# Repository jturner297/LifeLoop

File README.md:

# LifeLoop iOS App Documentation

## Overview
LifeLoop is an iOS application built with SwiftUI, integrating Bluetooth Low Energy (BLE) hardware telemetry monitoring, location services via CoreLocation, AWS Amplify with Cognito User Pools and AppSync GraphQL services for family health monitoring, hardware check-in pinging, real-time alert subscriptions, and emergency dispatching.

---

## Architecture & Core Components

### 1. Application Lifecycle & Configuration
* **App Initialization (`LifeLoopApp`):** Configures AWS Amplify (Auth and API plugins) and requests user notification authorizations (`.alert`, `.sound`, `.badge`) on app launch.
* **Bundle Identifier:** Configured dynamically via Xcode build target settings.

### 2. UI & User Flows

#### Root Navigation & Onboarding (`AppRootView`, `AccountSetupView`, `WelcomeView`)
* **Initial Setup Flow:**
  * If account setup is incomplete, the app presents `AccountSetupView` for AWS Cognito authentication (sign in, sign up, email verification code, password reset, challenge/MFA, or option to skip/continue without an account).
  * If account setup is complete but onboarding has not finished, `WelcomeView` prompts the user for their name, optional phone number, email address, and contact sharing consent.
  * Once onboarded, the app displays the main tab interface (`ContentView`).

#### Main Application Navigation (`ContentView`)
* **Tab Navigation:** Houses a 4-tab bottom navigation interface:
  1. **Home:** Main dashboard featuring user greeting, member/device search bar, view filters (Home, Family, Map), local device quick cards, manual "Call Help" emergency button, persistent emergency cancellation failure cards, and group member lists.
  2. **Devices:** Lists all saved LifeLoop BLE hardware peripherals, connection statuses, battery levels, and controls for connecting new peripherals.
  3. **Groups:** Displays family groups, invitation codes, member management, call contacts, and shared device configurations.
  4. **Profile:** Displays user profile details, privacy settings, notification configurations, and account management options.

#### Home Tab (`ContentView`)
* **Manual Emergency Call:** Provides a prominent "Call Help" button to initiate the emergency countdown (`EMSTimerManager`) and issue an `SOS` command to connected BLE devices.
* **Cloud Cancellation Warning Card:** Displays a prominent yellow warning card directly above the emergency button if a cloud emergency cancellation attempt fails on AWS, allowing the wearer to retry cloud cancellation explicitly without restarting an alert.
* **Search & Filters:** Enables filtering by Home view, Family member cards, or interactive group map view.

#### Devices Tab & Device Profiles (`ContentView`, `DeviceProfileSheet`, `AddDeviceSheet`)
* **BLE Device List:** Displays saved hardware peripherals, live heart rate (BPM), connection status (Connected, Connecting, Offline), and low battery warnings (<= 10%).
* **Add Device Sheet (`AddDeviceSheet`):** Scans for nearby LifeLoop BLE peripherals using `BLEMonitor`, listing discovered devices for one-tap pairing.
* **Device Profile Sheet (`DeviceProfileSheet`):** Shows detailed hardware state, battery level, live BPM, coordinates, last update timestamp, location map preview, raw BLE text payload, connection log, option to rename the device, and an explicit removal alert confirmation that disconnects and purges saved peripheral references.

#### Groups & Family Management (`GroupsView`, `GroupDetailView`, `FamilyManagementViews`)
* **Group Management:**
  * **Create & Join:** Users can create new family groups or join existing ones using an alphanumeric invitation code.
  * **Group Details:** Displays invitation code sharing options, local group nickname customization, list of family members, emergency call contacts, and shared device configurations.
* **Members & Roles (`FamilyMembersView`):**
  * Displays group members and assigned roles (`CREATOR`, `ADMIN`, `MEMBER`).
  * Admin and Creator roles can modify member roles, remove members, or block/unblock users.
* **Emergency Call Contacts (`FamilyContactsView` & `ContactEditor`):**
  * Allows managing up to 10 emergency call contacts per family group.
  * Contact addition requires explicitly validating the contact's name, phone number (E.164 format), and user consent confirmation.
* **Shared Devices (`GroupSharingView`):**
  * Controls which local BLE devices are shared with specific family groups.
* **Member Details & Check-In (`MemberInfoView`):**
  * Shows a family member's telemetry, BPM, online status, reverse-geocoded street address, interactive location map (`MemberMap`), and status of active check-in requests.
  * Includes a **"Send 'Check-In' Ping"** action to send a hardware check-in prompt to the target member's device.

#### Profile & Settings (`ProfileView`, `SettingsView`, `NotificationsView`)
* **User Profile (`ProfileView`):** Displays user initials/avatar, joined family count, and navigation to settings sections.
* **Personal & Privacy Settings (`SettingsView`):**
  * Edits display name, optional birthday (automatically updating calculated user age), phone number, email address, and contact sharing consent.
  * **Privacy Toggles:** Global toggles for `Share location` (`com.lifeloop.family.locationSharingEnabled`) and `Share device information` (`profile.shareDeviceInformation`).
* **Notification Settings (`NotificationsView`):**
  * Configures emergency alerts, call-workflow status updates, and sound toggles.
  * Displays system authorization status, provides a direct link to iOS App Settings, and includes a test notification trigger.

#### Emergency Overlay, Cancellation & Dispatch Status (`EMSCountdown`, `SOSAlertStatusView`)
* **Emergency Countdown (`EMSCountdown` / `EmergencyCountdownScreen`):**
  * Full-screen emergency presentation triggered automatically when a fall or cardiac abnormality is detected, or when manual SOS is pressed.
  * Displays a 30-second countdown ring, trigger reason, dynamic font sizing, accessibility reduce-motion awareness, and an explicit **"I’m OK — Cancel alert"** button.
* **Cancellation Feedback & Retry Alert:**
  * If the wearer cancels an alert but the AWS GraphQL cancellation mutation fails, the screen presents a "Cancellation Unconfirmed" alert prompt with options to retry cancellation or dismiss, ensuring the wearer is explicitly informed that emergency contacts may still be notified.
* **Alert Status (`SOSAlertStatusView`):**
  * Full-screen view presented after the countdown expires while the alert is active on AWS AppSync.
  * Informs the user of dispatch progress, grace period status, and option to request cancellation before emergency calls begin.

---

### 3. Design System & Styling (`LoopStyle`, `LifeLoopBrand`)
* **Color Palette:**
  * `LoopStyle.green` (`#38FF14` / RGB 0.22, 1.0, 0.08)
  * `LoopStyle.mint` (Light background accent)
  * `LoopStyle.background` (Off-white page background)
  * `LoopStyle.ink` (Dark text color)
* **Components & Modifiers:**
  * `.loopCard()`: Styled rounded card container for content blocks.
  * `.loopPage()`: Standard background and tint styling for views.
  * `ProfileAvatar`: Circle avatar rendering initials or fallback icon.
  * `MemberMap`: Standard SwiftUI `Map` wrapper showing member coordinates and fallback states.
  * `LandscapeArt`: Vector gradient and mountain landscape illustration.

---

### 4. Bluetooth Low Energy Integration & Hardware Firmware (`BLEMonitor` & `UpdatedNrfCode.ino`)

#### Hardware Firmware & Hardware State Machine (`UpdatedNrfCode.ino`)
* **Hardware Sensors:** Operates on Arduino-compatible nRF hardware with an LSM6DS3 IMU for accelerometer data and a MAX30105 optical pulse sensor for heart rate DSP. Runs an Edge Impulse Machine Learning model for fall classification.
* **Firmware State Machine (`FallDetection` enum):**
  * `Normal (0)`: Standard monitoring state.
  * `Recovering (3)`: Post-impact observation window.
  * `Emergency (4)`: Fall/Emergency state; flashes red LED and activates 3000 Hz buzzer tone.
  * `Ping (5)`: Check-in request state; flashes blue LED and activates 2000 Hz buzzer tone.
* **Hardware BLE Commands (Received via RX Characteristic):**
  * `"CANCEL"`: Resets state to `Normal (0)`, turns off buzzer, and restores default LEDs.
  * `"SOS"`: Transitions state directly to `Emergency (4)`, activates red LED and 3000 Hz buzzer.
  * `"PING"`: Transitions state to `Ping (5)`, activates blue LED and 2000 Hz buzzer. Pressing the physical hardware button (hold >= 500 ms) acknowledges the check-in and resets state to `Normal (0)`.

#### Hardware BLE Characteristics
* **Service UUID:** `6E400001-B5A3-F393-E0A9-E50E24DCCA9E`
* **TX Characteristic (Notify | Read):** `6E400003-B5A3-F393-E0A9-E50E24DCCA9E` (streams payload: `BPM:%.1f|State:%d\n`).
* **RX Characteristic (Write | Write Without Response):** `6E400002-B5A3-F393-E0A9-E50E24DCCA9E`.

#### iOS BLE Central Manager (`BLEMonitor`)
* **Connection Maintenance (`maintainConnections`):** Automatically scans for missing saved devices and retrieves/reconnects known peripherals unless manually disconnected. State restoration is supported via `LifeLoopCentralManager` restore key.
* **Telemetry Parsing:** Parses standard `BPM:%.1f|State:%d` payloads or JSON structures. Extracts heart rate (`bpm`, `heartrate`, `hr`), state, battery level, and optional location coordinates.
* **Emergency Detection:** Automatically triggers the local countdown timer (`EMSTimerManager.shared.startCountdown`) upon detecting cardiac abnormalities (BPM between 1 and 40) or severe fall state (`State 4`).
* **Device Fall Cancellation:** Detects when the wearer manually cancels an emergency on the physical hardware button (transition from State 3/4 to State 0 without an app cancel pending) and posts a `DeviceCancellationRequest`.
* **Ping Acknowledgment:** Detects when a device in `Ping` state (State 5) transitions to `Normal` (State 0), clears active ping flags, updates sequence counters, and posts a `.lifeLoopPingAcknowledged` notification.
* **BLE Command Methods:**
  * `sendSOSCommand()`: Writes `"SOS"` to the RX characteristic of connected peripherals.
  * `sendCancelCommand()`: Writes `"CANCEL"` to connected peripherals.
  * `sendPingCommand(deviceID:)`: Queues and writes `"PING"` to target or all known peripherals.

---

### 5. Emergency Management (`EMSTimerManager`, `EmergencyAlarmManager`)
* **Countdown Manager (`EMSTimerManager`):**
  * Controls the 30-second emergency countdown timer when cardiac, fall, or manual SOS events occur.
  * Holds reference to `triggerDeviceID`, `triggerReason`, and `callDeadline`.
  * `synchronizeCallDeadline(_ date: Date)`: Synchronizes the local timer deadline with the earliest call time returned by AWS backend alerts.
* **Audio & Haptic Alarm (`EmergencyAlarmManager`):**
  * Pre-loads the emergency alarm audio track into memory at app boot without activating the system audio session.
  * **Lazy Audio Activation & Prioritization:** Dynamically activates `AVAudioSession` with `.playback` category and `.duckOthers` option only when `startAlarm()` is executed during an active emergency, ducking external audio (e.g. Spotify/Apple Music).
  * **Haptic Vibration Loop:** Uses a dedicated `UIImpactFeedbackGenerator` with `.heavy` style triggered on a 0.6-second repeating timer alongside system vibrations.
  * **Audio Session Cleanup:** Calling `stopAlarm()` halts playback, invalidates the haptic timer, resets track timing, and explicitly deactivates the audio session with `.notifyOthersOnDeactivation` to immediately restore background audio volume.

---

### 6. Family Telemetry, Check-Ins & Synchronization (`FamilyDeviceManager`, `LoopNotifications`)
* **Telemetry Upload & Link Optimization:**
  * Periodically syncs connected device telemetry (BPM, state, GPS coordinates, location sharing preferences, online status) with AWS AppSync for linked family devices.
  * Maintains an in-memory `linkedDeviceKeys` set cache (`\(code):\(deviceID):\(displayName)`) to execute `linkDevice` GraphQL mutations only once per device connection, eliminating redundant AWS write operations during continuous telemetry streams.
* **Reverse Geocoding:** Converts latitude and longitude coordinates into structured street address using `CLGeocoder`, caching results per device.
* **Real-Time Subscription Management:**
  * **Check-In Subscriptions (`ensureCheckInSubscription`):** Listens to GraphQL WebSocket updates (`onCheckInChange`) for prompt acknowledgment.
  * **Alert Subscriptions (`ensureAlertSubscription`):** Subscribes to real-time GraphQL WebSocket alert changes (`onAlertChange`) via `apiClient.subscribeToAlerts(code:)`. Immediately processes incoming alerts, updates active group alert states, and passes alert payloads directly to `LoopNotifications.shared.receive([alert])` without polling delays.
  * **Lifecycle Cleanup:** Cancels and resets WebSocket subscription sequences (`activeCheckInSequence`, `activeAlertSequence`) when leaving groups or invoking `stopSharing()`.
* **Check-In PING Management:**
  * `requestCheckIn(for:)`: Issues a `sendPing` GraphQL mutation to prompt a specific device.
  * `acknowledgePing(checkInID:)`: Issues an `acknowledgePing` GraphQL mutation once the hardware button press is recognized.
* **Alert Lifecycle & Cancellation:**
  * `sendMyEmergencyAlert`: Calls AWS AppSync `startEmergency` mutation with stable alert IDs, location coordinates, and dispatch reason.
  * `cancelMyOwnEmergency` / `cancelAlert` / `cancelEmergency`: Calls AWS AppSync `cancelEmergency` mutation to cancel pending alerts before emergency calls begin.
* **Local & Notification Center Management (`LoopNotifications`):**
  * Manages iOS local user notifications for family alerts and status updates (`FAMILY_ALERT` category).
  * Parses notification response deep links to navigate directly to the target family group.

---

### 7. Cloud Infrastructure & Networking (`FamilyAPIClient`, AWS Amplify)
Communicates with AWS AppSync GraphQL API backend using Amplify API plugin with AWS Cognito User Pools authorization (`AMAZON_COGNITO_USER_POOLS`).

* **Authentication & Auth Plugin:**
  * User Pool ID: `us-east-2_zO8kdjTEs`
  * App Client ID: `si1qof5nhh76a6gguldcth0nn`
  * Region: `us-east-2`
  * Auth Flow: `USER_SRP_AUTH`

* **GraphQL API Operations (`FamilyAPIClient`):**
  * **Group & Membership Management:**
    * `createFamily(displayName:)`: Creates a new family group.
    * `joinFamily(code:displayName:)`: Joins a family group via invitation code.
    * `myFamilies()`: Fetches families the authenticated user belongs to.
    * `members(code:)` / `blockedMembers(code:)`: Retrieves group members and blocked users.
    * `setRole(code:userID:role:)`: Modifies member role (`CREATOR`, `ADMIN`, `MEMBER`).
    * `membershipAction(_:code:userID:)`: Executes membership mutations (`leaveFamily`, `removeMember`, `unblockMember`).
  * **Emergency Call Contacts:**
    * `contacts(code:)`: Retrieves configured emergency contacts for a group.
    * `saveContact(code:contactID:name:phone:)`: Creates (`addContact`) or updates (`updateContact`) emergency contacts.
    * `deleteContact(code:contactID:)`: Deletes an emergency contact.
  * **Telemetry & Devices:**
    * `linkDevice(_:)`: Associates a BLE peripheral with a family group code.
    * `uploadTelemetry(_:)`: Transmits `FamilyTelemetryPayload` updates.
    * `fetchFamilyDevices(groupCode:)`: Queries current member device statuses, telemetry, and location data.
  * **Alerts & Check-Ins:**
    * `startEmergency(_:)`: Dispatches `StartEmergencyInput` to initiate emergency call workflows.
    * `cancelEmergency(alertID:)`: Cancels an active emergency alert.
    * `alerts(code:)`: Queries recent alerts (`alertsForGroup`) for a family group.
    * `sendPing(code:targetDeviceID:)` / `acknowledgePing(checkInID:)`: Sends or acknowledges check-in pings.
    * `subscribeToCheckIns(code:)`: Real-time subscription to `onCheckInChange`.
    * `subscribeToAlerts(code:)`: Real-time subscription to GraphQL `onAlertChange` events.

---

### 8. Location Services (`LocationManager`)
* **Location Tracking:** Manages user permissions, continuous positioning updates via CoreLocation, and background location updates.
* **Coordinates Integration:** Supplies real-time latitude and longitude data for telemetry sync, map rendering, and emergency alert payloads when location sharing is enabled.

---

### 9. Infrastructure & Codebase Optimizations

#### Key Audits & Fixes (`ANALYSIS_REPORT.md`)
* **Cloud Alert Cancellation Feedback:** Resolved state teardown issue during countdown dismissal by surfacing unconfirmed cancellations via native alert dialogs and Home view retry buttons.
* **Audio Session Priority & Deactivation:** Prevents background audio ducking at app launch by deferring `AVAudioSession` activation to active siren events and explicitly releasing the session on stop.
* **Real-time Alert Notifications:** Replaced polling mechanisms with real-time AWS AppSync GraphQL WebSocket subscriptions (`onAlertChange`) for instant caregiver emergency notifications.
* **GraphQL Write Reduction:** Implemented key caching for device linking to prevent unnecessary repeat `linkDevice` mutations during live device telemetry streaming.

#### Automated Documentation
* **Auto-Docs Workflow (`.github/workflows/auto-docs.yml`):** Utilizes Gemini CLI (`gemini-3.6-flash` model) for automated documentation maintenance upon repository pushes. Configured to maintain and commit updates directly to `README.md`.

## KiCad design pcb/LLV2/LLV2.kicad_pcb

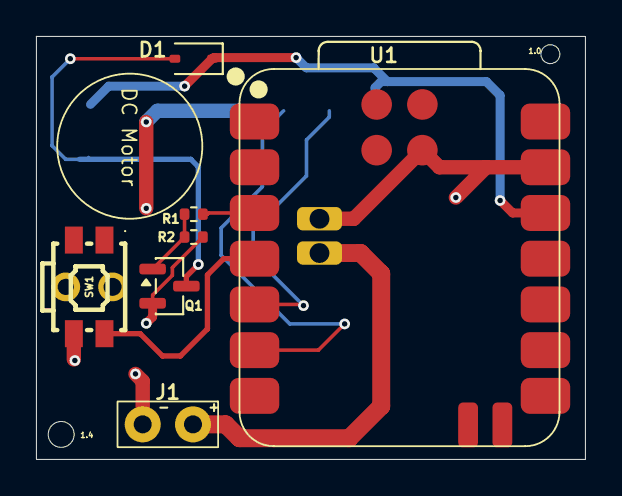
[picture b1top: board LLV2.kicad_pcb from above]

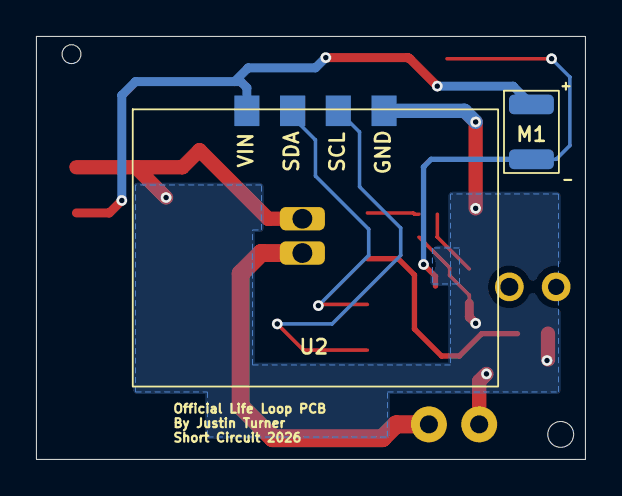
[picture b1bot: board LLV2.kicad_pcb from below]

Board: 2 copper layers, 30.5 x 23.5 mm, 9 parts (2 on the bottom side), 9 nets.

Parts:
D1: 1N4148W; D_SOD-323
J1: Conn_01x02; Wire Pads
M1: Motor_DC; Battery_Copper_Pads
Q1: AO3400A; SOT-23
R1: 1K; R_0402_1005Metric
R2: 100K; R_0402_1005Metric
SW1: SW_Push; KEY-SMD_4P-L4.8-W4.6-P1.70-LS6.2
U1: XIAO-nRF52840-SMD
U2: MAX30102; MAX30102_SMD

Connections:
+3V3: D1.1 (K), M1.1 (+), U1.12 (3V3_OUT), U2.11 (VDD)
GND: J1.2, Q1.2 (S), R2.2, SW1.1, U1.13 (GND), U1.18 (GND), U1.20 (GND), U2.12 (GND)
unnamed: D1.2 (A), M1.2 (-), Q1.3 (D)
unnamed: J1.1, U1.19 (VBAT)
unnamed: Q1.1 (G), R1.1, R2.1
unnamed: R1.2, U1.3 (D2)
unnamed: SW1.2, U1.4 (D3)
unnamed: U1.5 (D4), U2.3 (SDA)
unnamed: U1.6 (D5), U2.2 (SCL)

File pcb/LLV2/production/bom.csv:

Designator,Footprint,Quantity,Value,LCSC Part #
D1,D_SOD-323,1,1N4148W,
J1,Wire Pads,1,Conn_01x02,
M1,Battery_Copper_Pads,1,Motor_DC,
Q1,SOT-23,1,AO3400A,
R1,0402,1,1K,
R2,0402,1,100K,
SW1,KEY-SMD_4P-L4.8-W4.6-P1.70-LS6.2,1,SW_Push,
U1,XIAO-nRF52840-SMD,1,XIAO-nRF52840-SMD,
U2,MAX30102_SMD,1,MAX30102,

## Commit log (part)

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2026-04-22 Add placeholder files for code
2026-04-22 Add initial README with project description and logo
2026-04-22 Updated product logo
2026-04-24 Add gps code
2026-04-25 Add initial fall detection prototype
2026-04-26 Adjusted accelerometer sensitivity thresholds for improved drop detection. Decreased delay in order to reduce chances of missing falls.
2026-04-27 Complete GPS code
2026-04-28 add ble code
2026-04-28 Initial Heart Rate Code
2026-04-28 Life_Loop_Bluetooth.ino
2026-04-30 Updated code that introduces state LEDs for easier understanding for users.
2026-04-30 Removed .DS_Store and added it to .gitignore.
2026-05-10 Added Final PoC Heart Rate Files
2026-05-10 Updated GPS code
2026-05-10 Initial Proof of Concept
